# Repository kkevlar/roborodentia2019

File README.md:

# Roborodentia 2019

Autonomous drive code for **Fold**, the second place robot for Cal Poly's annual autonomous robotics competition.

[Roborodentia Web Page](http://roborodentia.calpoly.edu/)

[Game Rules (2019)](https://docs.google.com/document/d/1yxtSJe29Ct2Tb8KmzMLPe1f2cj2fBtazdUNPZ5FT0Tg/edit)

[Roborodenia 2018 (first place)](https://github.com/kkevlar/roborodentia2018)

Authors: Kevin Kellar and Derick Louie

## Usage

This drive source code was written for an Arduino Uno, and it depends on the standard Arduino libraries. 

It also depends on the following other Arduino libraries:
* Wire
* [Adafruit_MotorShield](https://github.com/adafruit/Adafruit_Motor_Shield_V2_Library)
* [LiquidCrystal_I2C](https://github.com/kkevlar/LiquidCrystal_I2C)
* Servo

If these libraries are installed, this project should be easily compilable / uploadable by using Arduino IDE to open FOLD.ino.

The Makefile should allow for easy (mileage may vary) compilation / uploading of the drive code using [Arduino Makefile](https://github.com/sudar/Arduino-Makefile).

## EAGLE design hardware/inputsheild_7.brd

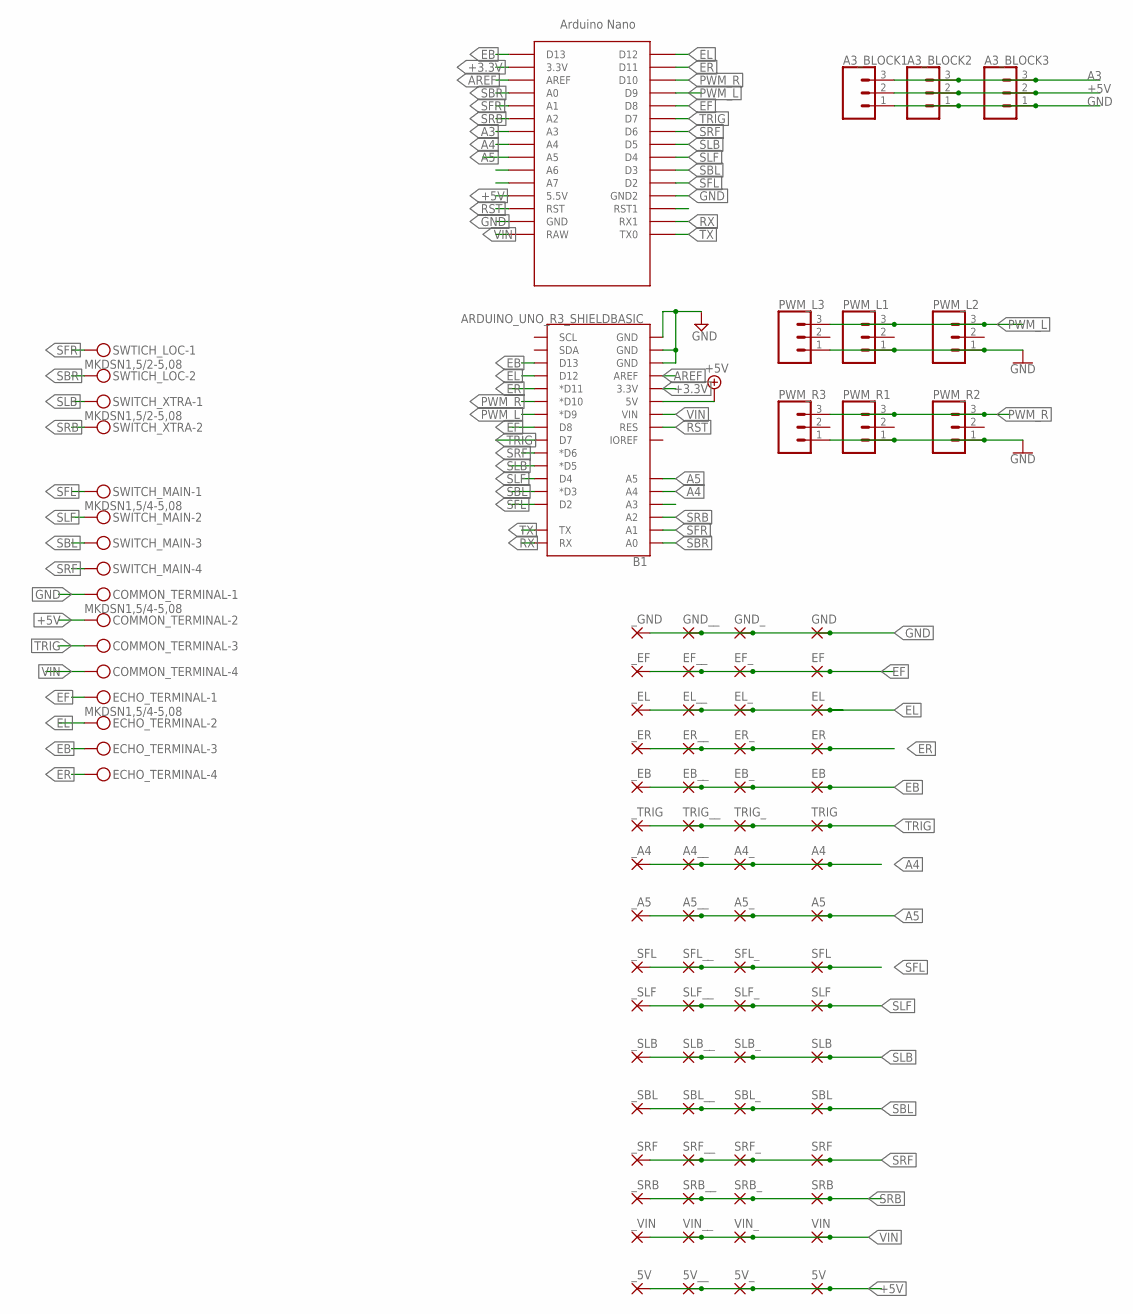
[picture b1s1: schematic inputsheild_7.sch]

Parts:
5V, 5V_, 5V__: SMD5; SMD2,54-5,08
A3_BLOCK1, A3_BLOCK2, A3_BLOCK3: CONN_03; 1X03
A4, A4_, A4__, A5, A5_, A5__: SMD5; SMD2,54-5,08
B1: ARDUINO_UNO_R3_SHIELDBASIC; UNO_R3_SHIELD
COMMON_TERMINAL: MKDSN1,5/4-5,08
EB: SMD5; SMD2,54-5,08
EB_: SMD5; SMD2,54-5,08
EB__: SMD5; SMD2,54-5,08
ECHO_TERMINAL: MKDSN1,5/4-5,08
EF: SMD5; SMD2,54-5,08
EF_: SMD5; SMD2,54-5,08
EF__: SMD5; SMD2,54-5,08
EL: SMD5; SMD2,54-5,08
EL_: SMD5; SMD2,54-5,08
EL__: SMD5; SMD2,54-5,08
ER: SMD5; SMD2,54-5,08
ER_: SMD5; SMD2,54-5,08
ER__: SMD5; SMD2,54-5,08
GND: SMD5; SMD2,54-5,08
GND_: SMD5; SMD2,54-5,08
GND__: SMD5; SMD2,54-5,08
PWM_L1, PWM_L2, PWM_L3: CONN_03; 1X03
PWM_R1, PWM_R2, PWM_R3: CONN_03; 1X03
SBL: SMD5; SMD2,54-5,08
SBL_: SMD5; SMD2,54-5,08
SBL__: SMD5; SMD2,54-5,08
SFL: SMD5; SMD2,54-5,08
SFL_: SMD5; SMD2,54-5,08
SFL__: SMD5; SMD2,54-5,08
SLB: SMD5; SMD2,54-5,08
SLB_: SMD5; SMD2,54-5,08
SLB__: SMD5; SMD2,54-5,08
SLF: SMD5; SMD2,54-5,08
SLF_: SMD5; SMD2,54-5,08
SLF__: SMD5; SMD2,54-5,08
SRB: SMD5; SMD2,54-5,08
SRB_: SMD5; SMD2,54-5,08
SRB__: SMD5; SMD2,54-5,08
SRF: SMD5; SMD2,54-5,08
SRF_: SMD5; SMD2,54-5,08
SRF__: SMD5; SMD2,54-5,08
SWITCH_MAIN: MKDSN1,5/4-5,08
SWITCH_XTRA: MKDSN1,5/2-5,08
SWTICH_LOC: MKDSN1,5/2-5,08
TRIG: SMD5; SMD2,54-5,08
TRIG_: SMD5; SMD2,54-5,08
TRIG__: SMD5; SMD2,54-5,08
U$1: NANO
VIN: SMD5; SMD2,54-5,08
VIN_: SMD5; SMD2,54-5,08
VIN__: SMD5; SMD2,54-5,08
_5V: SMD5; SMD2,54-5,08
_A4, _A5: SMD5; SMD2,54-5,08
_EB: SMD5; SMD2,54-5,08
_EF: SMD5; SMD2,54-5,08
_EL: SMD5; SMD2,54-5,08
_ER: SMD5; SMD2,54-5,08
_GND: SMD5; SMD2,54-5,08
_SBL: SMD5; SMD2,54-5,08
_SFL: SMD5; SMD2,54-5,08
_SLB: SMD5; SMD2,54-5,08
_SLF: SMD5; SMD2,54-5,08
_SRB: SMD5; SMD2,54-5,08
_SRF: SMD5; SMD2,54-5,08
_TRIG: SMD5; SMD2,54-5,08
_VIN: SMD5; SMD2,54-5,08

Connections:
+3.3V: B1.3.3V, U$1.3.3V
+5V: 5V.1, 5V_.1, 5V__.1, A3_BLOCK1.2, A3_BLOCK2.2, A3_BLOCK3.2, B1.5V, COMMON_TERMINAL.2, U$1.5V (5.5V), _5V.1
A3: A3_BLOCK1.3, A3_BLOCK2.3, A3_BLOCK3.3, U$1.A3
A4: A4.1, A4_.1, A4__.1, B1.A4, U$1.A4, _A4.1
A5: A5.1, A5_.1, A5__.1, B1.A5, U$1.A5, _A5.1
AREF: B1.AREF, U$1.AREF
EB: B1.D13, EB.1, EB_.1, EB__.1, ECHO_TERMINAL.3, U$1.D13, _EB.1
EF: B1.D8, ECHO_TERMINAL.1, EF.1, EF_.1, EF__.1, U$1.D8, _EF.1
EL: B1.D12, ECHO_TERMINAL.2, EL.1, EL_.1, EL__.1, U$1.D12, _EL.1
ER: B1.D11 (*D11), ECHO_TERMINAL.4, ER.1, ER_.1, ER__.1, U$1.D11, _ER.1
GND: A3_BLOCK1.1, A3_BLOCK2.1, A3_BLOCK3.1, B1.GND@0 (GND), B1.GND@1 (GND), B1.GND@2 (GND), COMMON_TERMINAL.1, GND.1, GND_.1, GND__.1, PWM_L1.1, PWM_L2.1, PWM_L3.1, PWM_R1.1, PWM_R2.1, PWM_R3.1, U$1.GND, U$1.GND1 (GND2), _GND.1
PWM_L: B1.D9 (*D9), PWM_L1.3, PWM_L2.3, PWM_L3.3, U$1.D9
PWM_R: B1.D10 (*D10), PWM_R1.3, PWM_R2.3, PWM_R3.3, U$1.D10
RST: B1.RES, U$1.RST
RX: B1.RX, U$1.RX1
SBL: B1.D3 (*D3), SBL.1, SBL_.1, SBL__.1, SWITCH_MAIN.3, U$1.D3, _SBL.1
SBR: B1.A0, SWTICH_LOC.2, U$1.A0
SFL: B1.D2, SFL.1, SFL_.1, SFL__.1, SWITCH_MAIN.1, U$1.D2, _SFL.1
SFR: B1.A1, SWTICH_LOC.1, U$1.A1
SLB: B1.D5 (*D5), SLB.1, SLB_.1, SLB__.1, SWITCH_XTRA.1, U$1.D5, _SLB.1
SLF: B1.D4, SLF.1, SLF_.1, SLF__.1, SWITCH_MAIN.2, U$1.D4, _SLF.1
SRB: B1.A2, SRB.1, SRB_.1, SRB__.1, SWITCH_XTRA.2, U$1.A2, _SRB.1
SRF: B1.D6 (*D6), SRF.1, SRF_.1, SRF__.1, SWITCH_MAIN.4, U$1.D6, _SRF.1
TRIG: B1.D7, COMMON_TERMINAL.3, TRIG.1, TRIG_.1, TRIG__.1, U$1.D7, _TRIG.1
TX: B1.TX, U$1.TX0
VIN: B1.VIN, COMMON_TERMINAL.4, U$1.RAW, VIN.1, VIN_.1, VIN__.1, _VIN.1

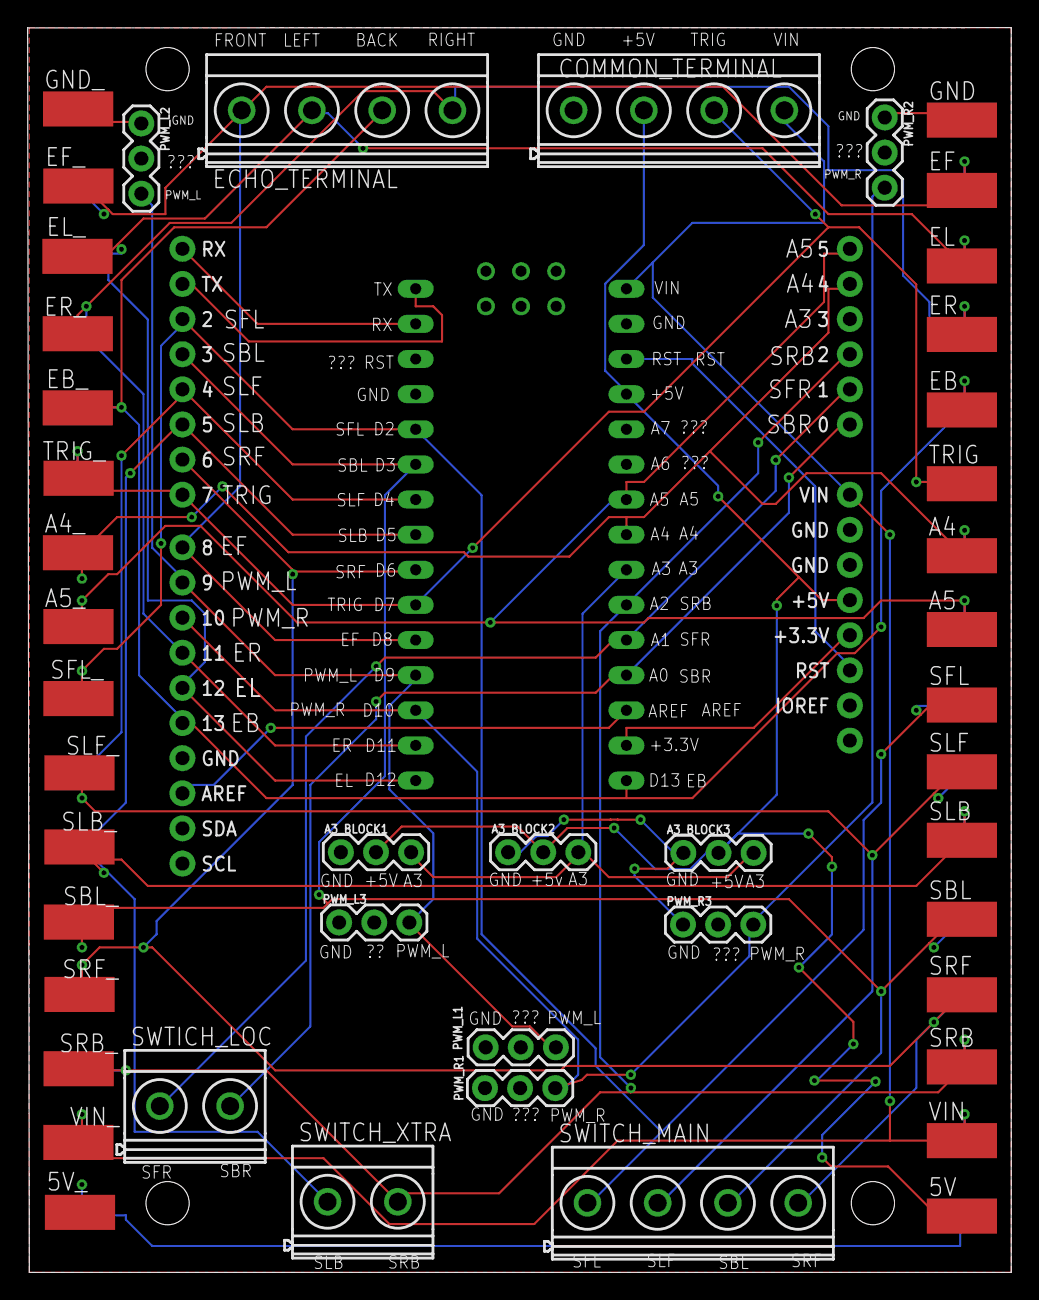
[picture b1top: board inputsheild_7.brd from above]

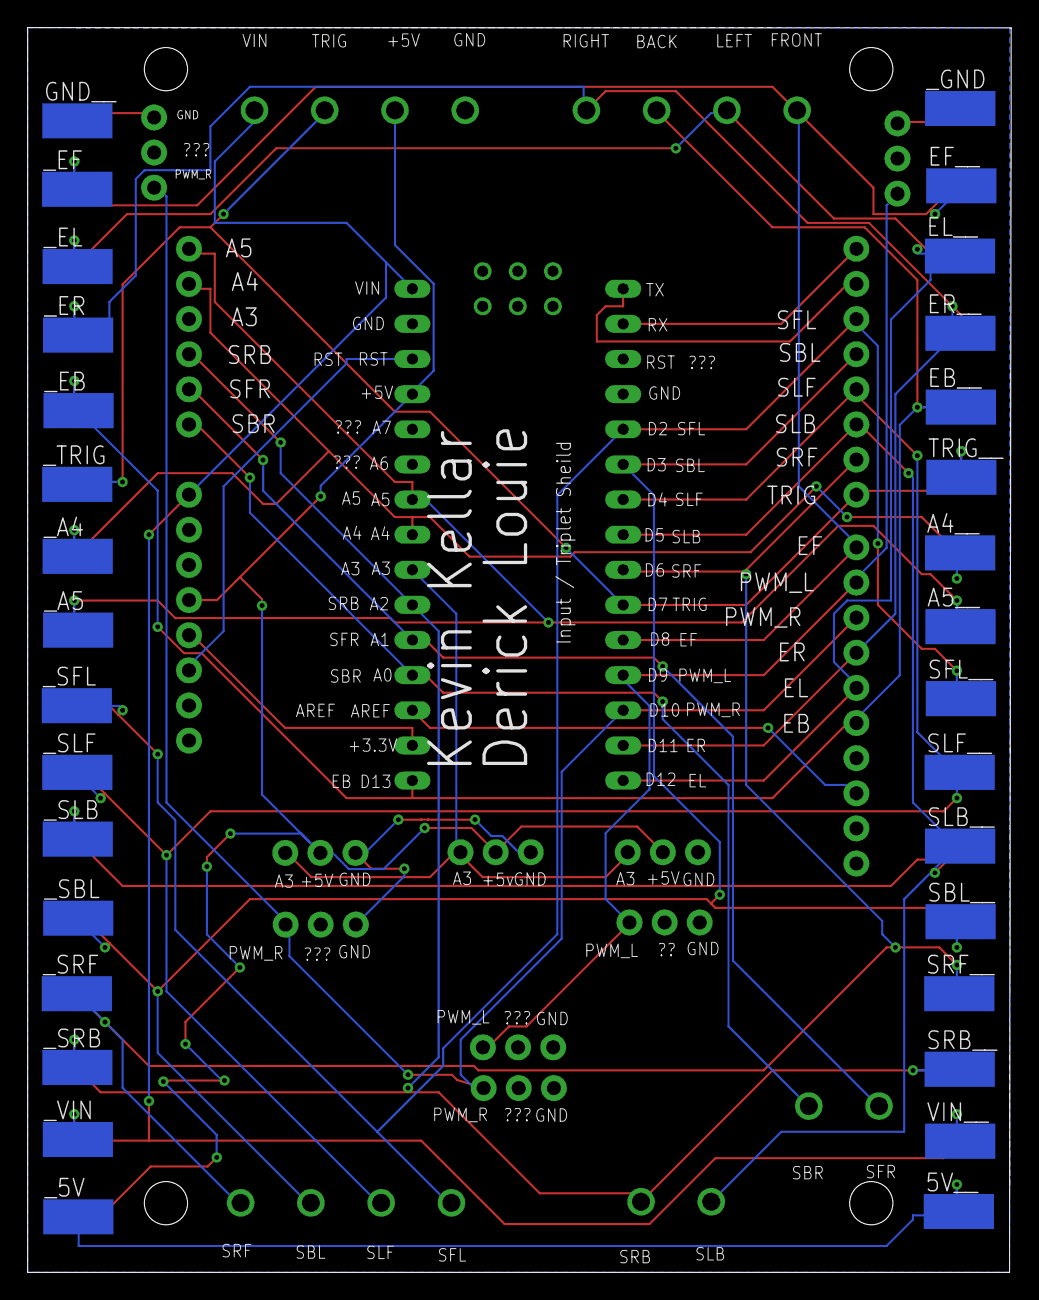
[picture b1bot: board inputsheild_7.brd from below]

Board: 2 copper layers, 71.1 x 90.0 mm, 80 parts (32 on the bottom side), 26 nets.

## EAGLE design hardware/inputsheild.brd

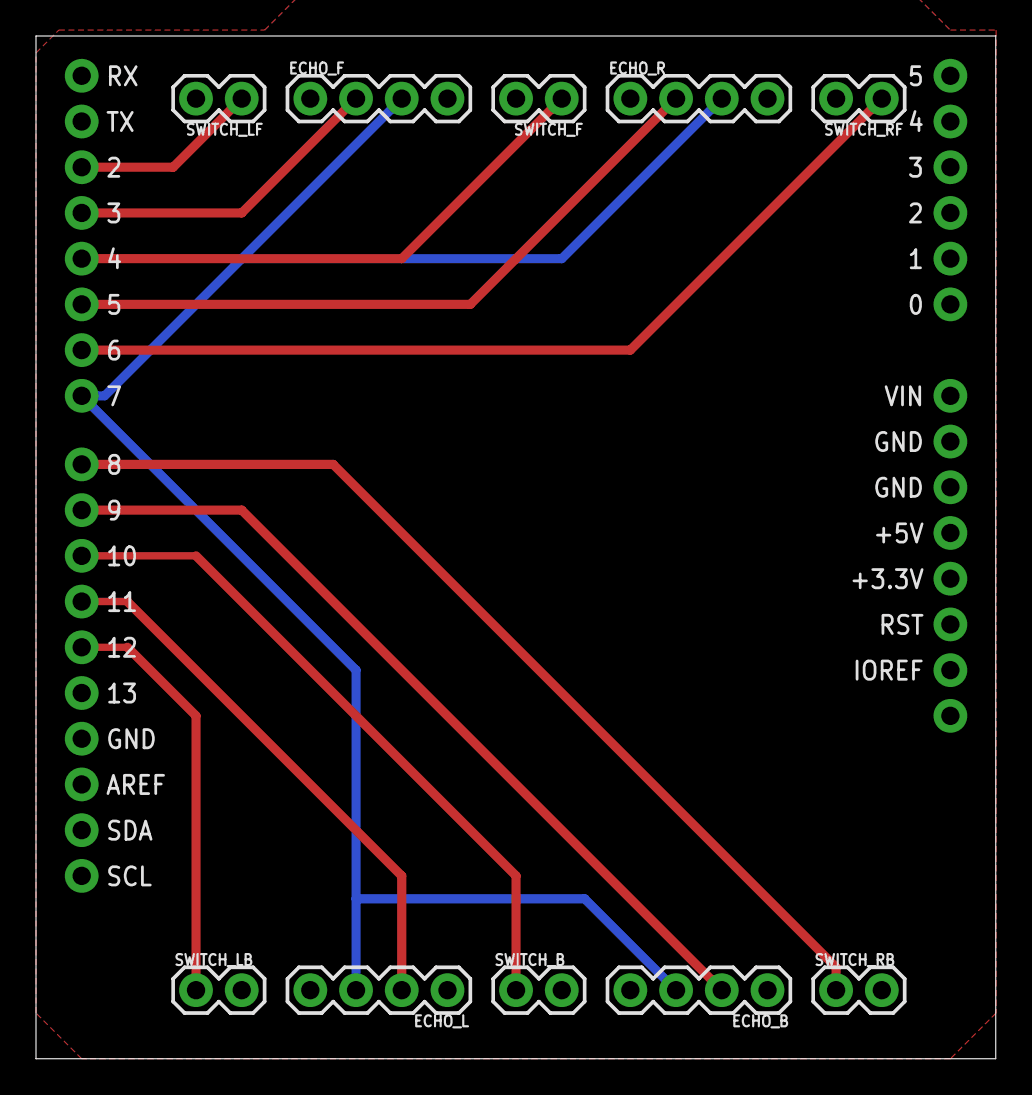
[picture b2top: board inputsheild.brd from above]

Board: 2 copper layers, 53.3 x 56.8 mm, 11 parts (0 on the bottom side), 13 nets.

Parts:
B1: ARDUINO_UNO_R3_SHIELDBASIC; UNO_R3_SHIELD
ECHO_B: 1X04
ECHO_F: 1X04
ECHO_L: 1X04
ECHO_R: 1X04
SWITCH_B: 1X02
SWITCH_F: 1X02
SWITCH_LB: 1X02
SWITCH_LF: 1X02
SWITCH_RB: 1X02
SWITCH_RF: 1X02

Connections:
+5V: B1.5V, ECHO_B.4, ECHO_F.4, ECHO_L.4, ECHO_R.4
D2: B1.D2, SWITCH_LF.1
D3: B1.D3, ECHO_F.2
D4: B1.D4, SWITCH_F.1
D5: B1.D5, ECHO_R.2
D6: B1.D6, SWITCH_RF.1
D8: B1.D8, SWITCH_RB.1
D9: B1.D9, ECHO_B.2
D10: B1.D10, SWITCH_B.1
D11: B1.D11, ECHO_L.2
D12: B1.D12, SWITCH_LB.1
GND: B1.GND@0, ECHO_B.1, ECHO_F.1, ECHO_L.1, ECHO_R.1, SWITCH_B.2, SWITCH_F.2, SWITCH_LB.2, SWITCH_LF.2, SWITCH_RB.2, SWITCH_RF.2
TRIG: B1.D7, ECHO_B.3, ECHO_F.3, ECHO_L.3, ECHO_R.3

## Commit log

2019-01-20 init commit
2019-01-21 added test drive code
2019-01-21 gcc test weird results
2019-01-21 ready to test on bot
2019-01-21 addded echo module
2019-01-21 i love this controller
2019-01-22 envy's fold
2019-01-23 added good roomba code
2019-01-27 good enough
2019-01-28 bookkeeping
2019-01-28 added testoptions
2019-02-03 SUCCESS wall
2019-02-04 fast wall hours!
2019-02-13 gcctest doesnt compile by default and nonblock p control progress
2019-02-13 added control module
2019-02-13 robust nonblock p control now takes a struct of args
2019-02-13 added default control struct fillers
2019-02-13 gcctest now interactive
2019-02-13 RENAME NSWE to FBLR
2019-02-13 made float comparisons more robust
2019-02-13 ez atan
2019-03-04 add inputsheild
2019-03-06 hardware update
2019-03-06 add main and test but they dont do anything
2019-03-08 fold just ands off to main or test
2019-03-08 new old robot drive wWOWOWOWOWO
2019-03-12 add echo tests
2019-03-12 rip limit switches
2019-03-12 drive vec combinations:
2019-03-12 pcontrol now no longer takes switch pin
2019-03-17 waaaa
2019-03-29 try inputshield 3
2019-03-29 so many jumpers in schematic
2019-03-29 wooo
2019-04-02 hardware
2019-04-02 rat obstacle course
2019-04-03 buffering within pcontrol. will it work?
2019-04-03 pos test
2019-04-05 more test drive code
2019-04-06 rat kitchen
2019-04-09 dericks holes
2019-04-19 so much
2019-04-19 work on sheild 6
2019-04-20 ready to route 6
2019-04-28 big reorganize
2019-04-29 changed wiring and resulting files
2019-04-29 added shoot and lcd modules
2019-05-04 lcd hello worldgit status
2019-05-05 single collection made
2019-05-05 collection victory lap
2019-05-05 new aim and collect modules- also fixed switch module
2019-05-09 inited shoot elements
2019-05-10 major aim logic - also fixed gcctest
2019-05-10 kinda finished aim not really:
2019-05-10 a few notes
2019-05-12 tested card diag on new bot today!
2019-05-13 tested pcontrol on new bot
2019-05-14 front porch befofre tues test
2019-05-14 code actually for first day of field testing
2019-05-15 happy with on tues night
2019-05-16 we night finished

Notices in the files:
parts and their libraries:
SparkFun-Boards: Licensing: Creative Commons ShareAlike 4.0 International - https://creativecommons.org/licenses/by-sa/4.0
